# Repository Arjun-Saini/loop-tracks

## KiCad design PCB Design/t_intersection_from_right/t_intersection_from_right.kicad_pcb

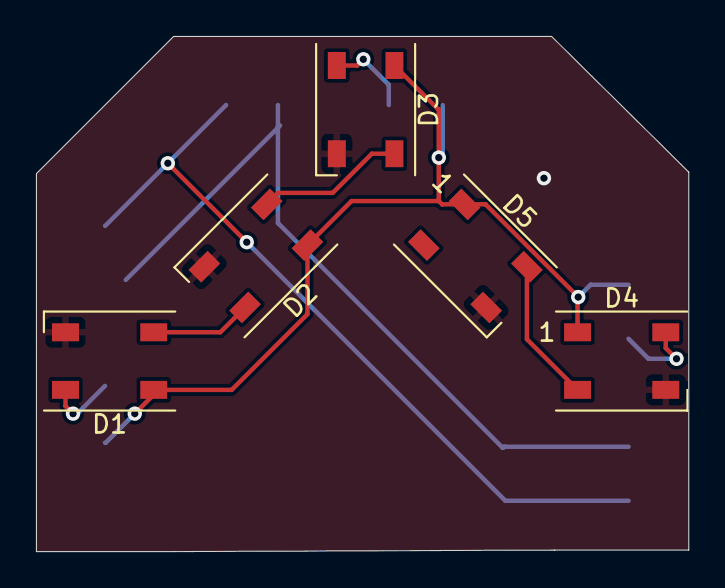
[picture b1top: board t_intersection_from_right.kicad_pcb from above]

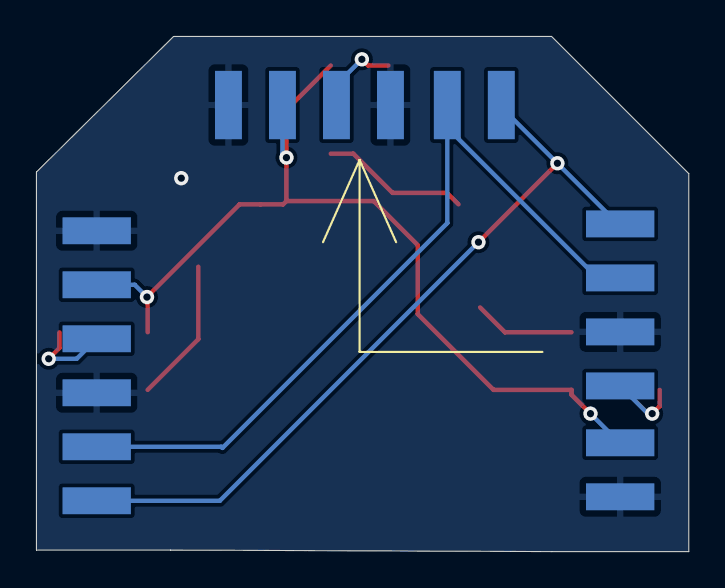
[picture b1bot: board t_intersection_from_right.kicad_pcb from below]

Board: 2 copper layers, 36.2 x 28.6 mm, 8 parts (3 on the bottom side), 10 nets.

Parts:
CN1, CN2, CN3: 1X4SMT; 1X4-SMT
D1, D2, D3, D4, D5: WS2812B; LED_WS2812B_PLCC4_5.0x5.0mm_P3.2mm

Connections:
+5V: CN1.5, CN2.2, CN3.2, D1.1 (VDD), D2.1 (VDD), D3.1 (VDD), D4.1 (VDD), D5.1 (VDD)
GND: CN1.3, CN1.6, CN2.1, CN2.4, CN3.1, CN3.4, D1.3 (VSS), D2.3 (VSS), D3.3 (VSS), D4.3 (VSS), D5.3 (VSS)
unnamed: CN1.1, CN2.6, CN3.6
unnamed: CN1.2, CN2.5, CN3.5
unnamed: CN1.4, D3.2 (DOUT)
unnamed: CN2.3, D1.4 (DIN)
unnamed: CN3.3, D4.4 (DIN)
unnamed: D1.2 (DOUT), D2.4 (DIN)
unnamed: D2.2 (DOUT), D3.4 (DIN)
unnamed: D4.2 (DOUT), D5.4 (DIN)

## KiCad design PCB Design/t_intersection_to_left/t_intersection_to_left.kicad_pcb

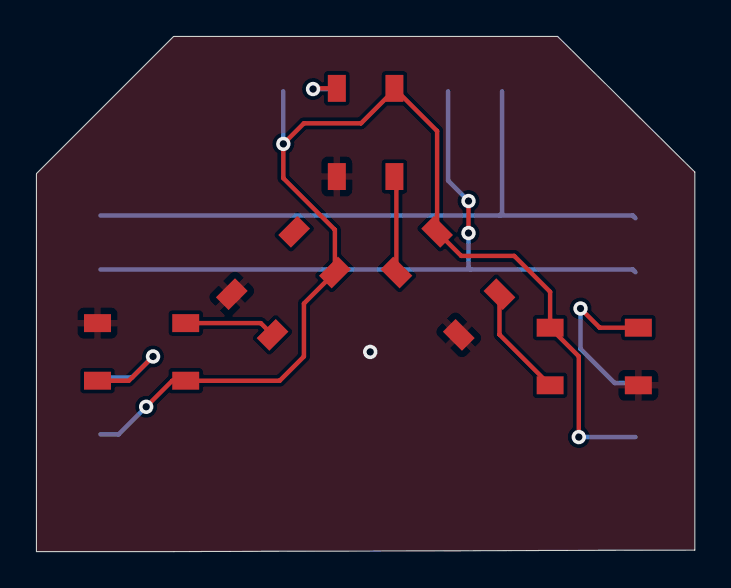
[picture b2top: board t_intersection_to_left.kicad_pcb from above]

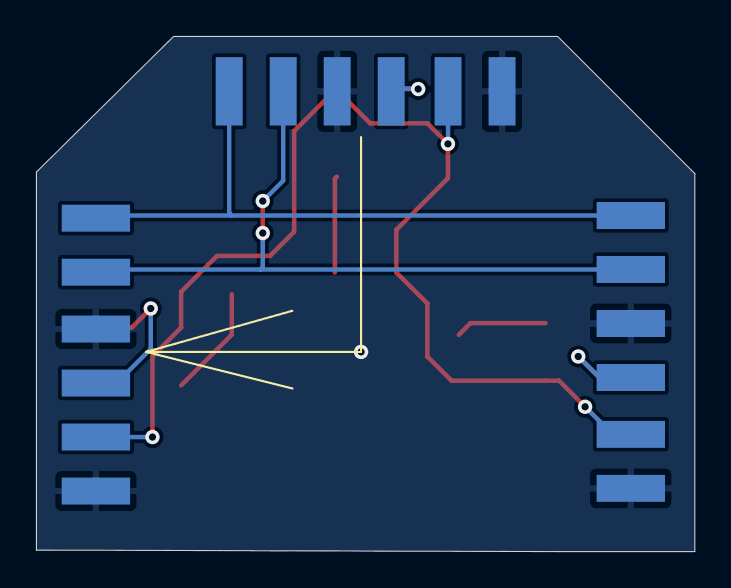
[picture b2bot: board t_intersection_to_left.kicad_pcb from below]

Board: 2 copper layers, 36.6 x 28.6 mm, 8 parts (3 on the bottom side), 10 nets.

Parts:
CN1, CN2, CN3: 1X4SMT; 1X4-SMT
D1, D3, D4, D6, D7: WS2812B; LED_WS2812B_PLCC4_5.0x5.0mm_P3.2mm

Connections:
+5V: CN1.5, CN2.2, CN3.2, D1.1 (VDD), D3.3 (VSS), D4.1 (VDD), D6.3 (VSS), D7.3 (VSS)
GND: CN1.3, CN1.6, CN2.1, CN2.4, CN3.1, CN3.4, D1.3 (VSS), D3.1 (VDD), D4.3 (VSS), D6.1 (VDD), D7.1 (VDD)
unnamed: CN1.1, CN2.6, CN3.6
unnamed: CN1.2, CN2.5, CN3.5
unnamed: CN1.4, D7.2 (DOUT)
unnamed: CN2.3, D3.4 (DIN)
unnamed: CN3.3, D4.4 (DIN)
unnamed: D1.4 (DIN), D4.2 (DOUT)
unnamed: D3.2 (DOUT), D6.4 (DIN)
unnamed: D6.2 (DOUT), D7.4 (DIN)
